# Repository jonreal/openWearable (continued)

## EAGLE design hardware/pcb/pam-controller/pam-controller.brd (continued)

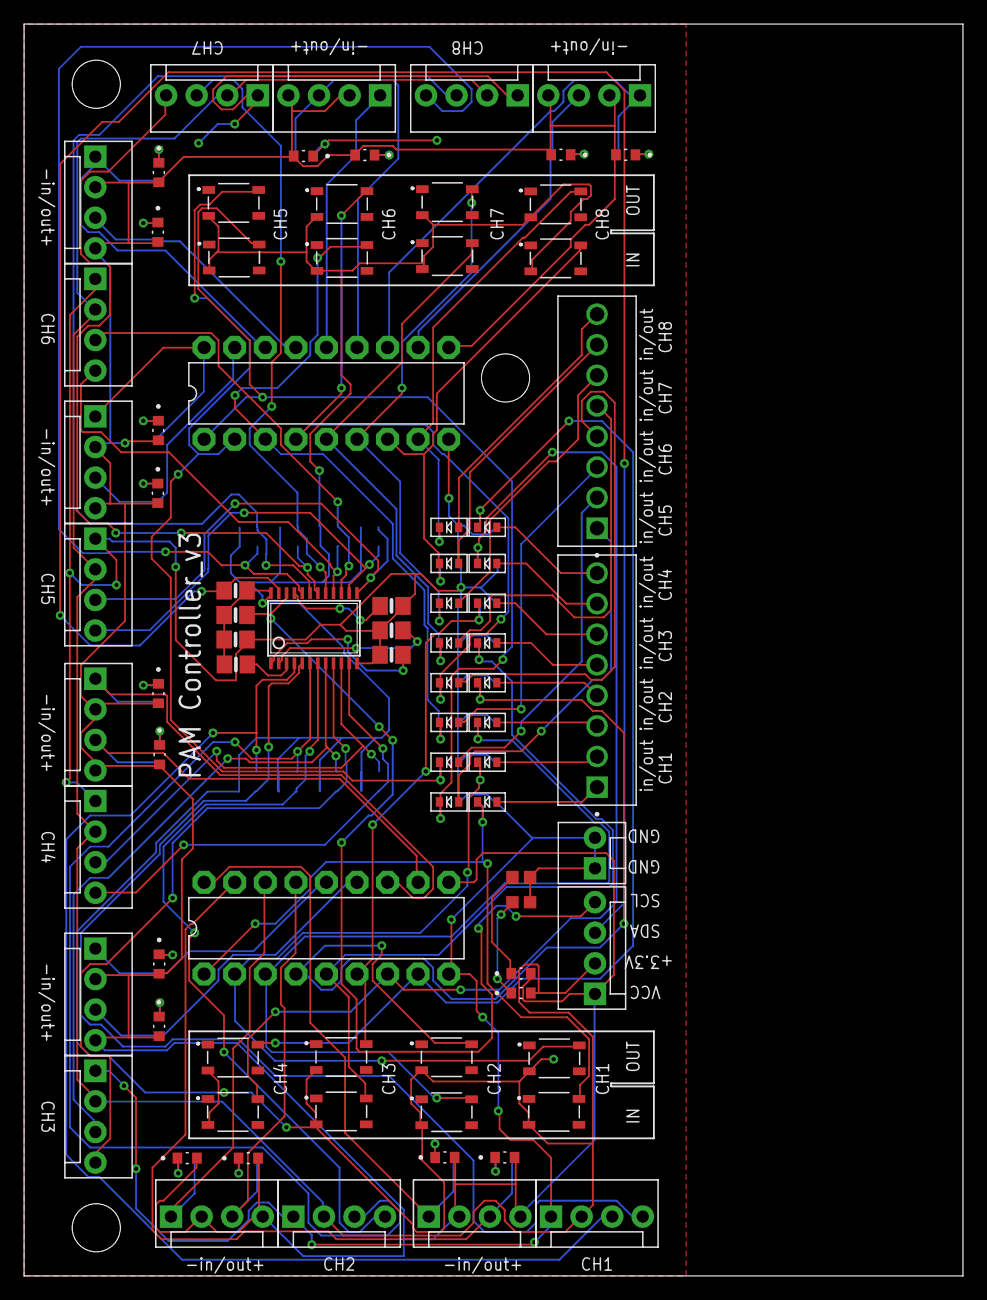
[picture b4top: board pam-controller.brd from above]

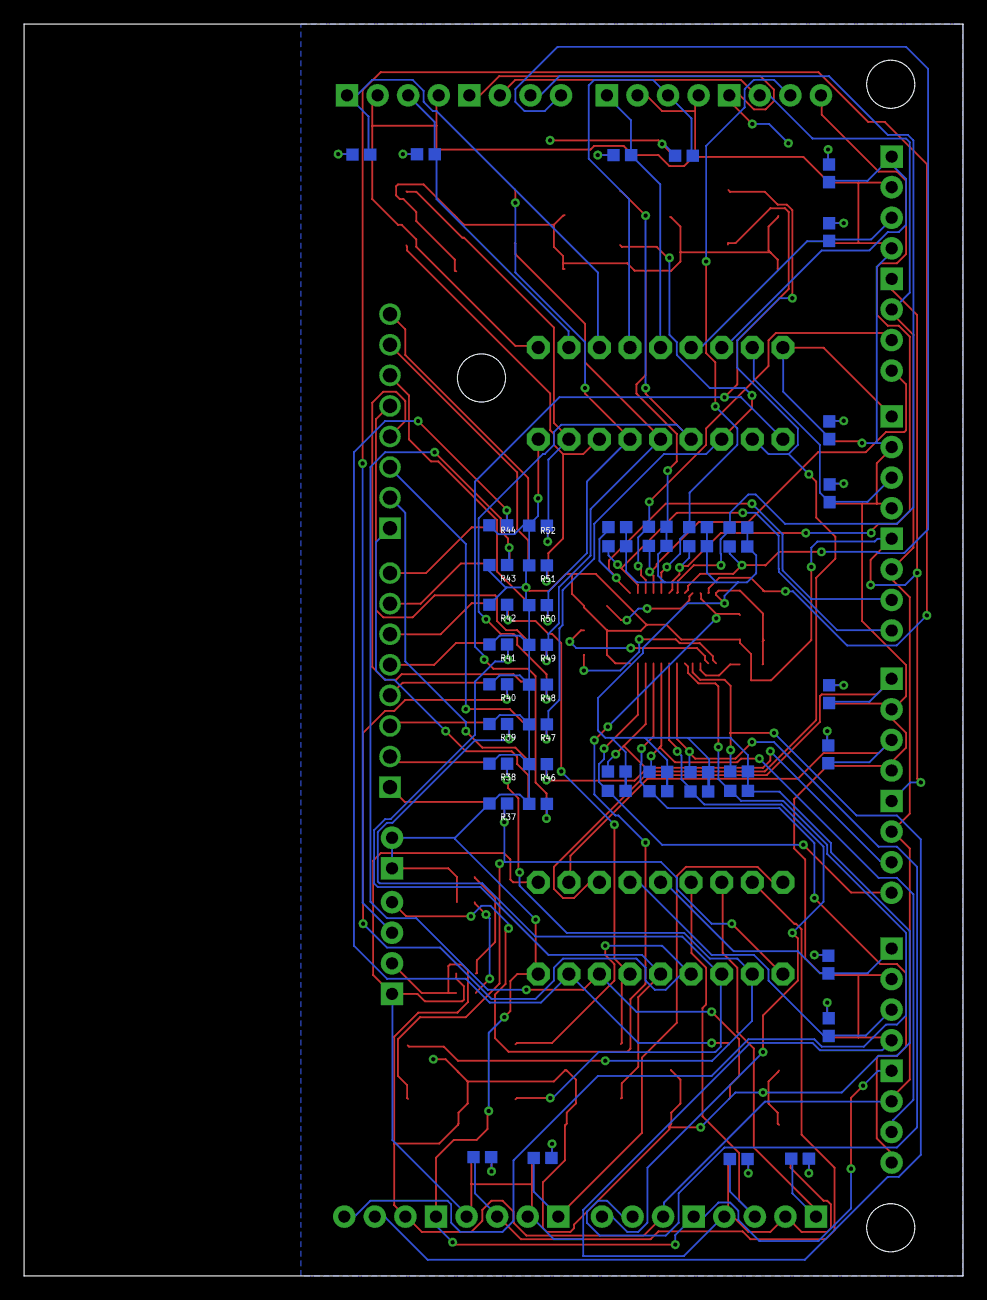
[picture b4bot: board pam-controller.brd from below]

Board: 2 copper layers, 78.0 x 104.0 mm, 130 parts (48 on the bottom side), 91 nets.

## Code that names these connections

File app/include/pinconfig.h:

#ifndef _PINCONFIG_H_
#define _PINCONFIG_H_

#define PWM_PIN     "P8_13"
#define ENB_PIN     "P8_15"
#define DIR_PIN     "P8_17"

#define ADC0        "P9_39"
#define ADC1        "P9_40"
#define ADC2        "P9_37"
#define ADC3        "P9_38"
#define ADC4        "P9_33"
#define ADC5        "P9_36"
#define ADC6        "P9_35"

#define RAD2DEG(X)    ((180.0/M_PI)*X)
#define DEG2RAD(X)    ((M_PI/180.0)*X)

#define ANGLE_OFFSET DEG2RAD(-10)


#endif

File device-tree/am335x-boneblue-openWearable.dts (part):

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	 */
	ehrpwm2_pins: pinmux_ehrpwm2_pins {
		pinctrl-single,pins = <
			AM33XX_PADCONF(AM335X_PIN_GPMC_AD8, PIN_OUTPUT, MUX_MODE4)		/* (U10) gpmc_ad8.ehrpwm2a - PWM_2A */
			AM33XX_PADCONF(AM335X_PIN_GPMC_AD9, PIN_OUTPUT, MUX_MODE4)		/* (T10) gpmc_ad9.ehrpwm2b - PWM_2B */
		>;
	};
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			AM33XX_PADCONF(AM335X_PIN_MCASP0_ACLKX, PIN_INPUT, MUX_MODE3)		/* (A13) mcasp0_aclkx.spi1_sclk */
			AM33XX_PADCONF(AM335X_PIN_MCASP0_FSX, PIN_INPUT, MUX_MODE3)		/* (B13) mcasp0_fsx.spi1_d0 */
			AM33XX_PADCONF(AM335X_PIN_MCASP0_AXR0, PIN_INPUT, MUX_MODE3)		/* (D12) mcasp0_axr0.spi1_d1 */
			/* AM33XX_PADCONF(AM335X_PIN_MCASP0_AHCLKR, PIN_INPUT, MUX_MODE3) */		/* (C12) mcasp0_ahclkr.spi1_cs0 */
			AM33XX_PADCONF(AM335X_PIN_ECAP0_IN_PWM0_OUT, PIN_INPUT, MUX_MODE2)	/* (C18) ecap0_in_pwm0_out.spi1_cs1 */
		>;
	};

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
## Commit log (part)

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2019-08-16 New branch
2019-08-16 Removed irrelevent apps from thumbsup branch
2019-08-16 Readme for thumbsup
2019-08-16 Removed makefile apps not related to thumbsup
2019-08-16 Readme for thumbsup directions
2019-08-16 Update README.md
    thumbs readme
2019-08-16 Update README.md
    updated readme
2019-08-16 Update README.md
    readme
2019-08-16 Add ctl to change base pressure
2019-08-21 update ros publisher to include sync state
2019-09-20 updated maxon driver
2019-09-24 Haptic module completed
2019-09-29 updated reflex to include minimum sensing pressure, added sine to fix16, added freq sweeps for sys ID
2019-09-30 Update README.md
    updated to include other possible ip addresses
2019-09-30 Updates to thumbsup
2019-10-01 Updates to chirp sweeps
2019-10-03 updated pin png
2019-10-04 updated haptics and sweeps and added tare encoder
2019-10-07 new app for haptuv evauations which includes a reflex instantiation, minor upgrades to reflex and device tree
2019-10-18 Emg updates, sig handling, hapit eval, this commit represent code for subject-014
2019-10-23 Emg complete, working on reflexes
2019-10-24 Updated haptic experiment, this commit is snapshot for exp subject 318
2019-10-28 Updating pwm-dac
2019-11-15 Myo reflex and step respone
2019-11-15 Experiment day commit before
2019-11-15 Commit before experiment
2019-11-15 Updated gui
2019-11-15 updated device tree
2019-11-15 gui stuff
2019-11-18 Upgrades on game play before experiment
2019-11-20 Commit before exp w s318
2019-11-25 Commit for exp s435
2019-11-26 Commit s410
2019-12-03 Commit s412
2019-12-04 Added imu to haptic experiment
2019-12-04 Updated reflex parameters
2019-12-04 Added delay in between i2c calls in imu update
2019-12-04 Commit for s410 note that removed imu during exp
2019-12-09 s435
2019-12-16 Updated m-file process data
2019-12-19 s408
2019-12-23 s422
2020-02-09 Some old changes
2020-02-09 updated the haptic tracking app
2020-07-01 new branch for pafp
2020-07-01 updated embedded_process
2020-07-01 minor
2020-07-01 Added updated embedded_process to this branch
2020-07-06 Updated maxon-sweep and tare-encoder for loading parameters to memory
2020-07-06 Updated pyplotter
2021-09-16 Weird bug from a long time ago I guess
2022-02-15 Branch for equiblrium-point-study
2022-02-16 Readme
2022-02-16 Removed hardware stuff that doesn't apply to this project
2022-07-13 fixed bugs in template
2022-08-11 Add pam-starecase for experimental eval of pams
2022-09-02 Pam starecase plus edits to template
2022-09-08 Updated maxon motor and tare to use the PruLoadParams method
2022-09-09 removed ROS from build, but stored old ros makefile
2022-09-09 Tools for PWM/motor calibration
2022-09-12 Updated haptic-tracking with new motor bias current argument
2022-09-21 Updated udp lib, hostname option
2022-09-21 Completed the udp upgrade and added python udplisterner for demo purposes
2022-09-22 Added py udp listner
2022-09-22 Pam cycle for cylic tests
2022-09-22 Edits
2022-09-23 Updated pam-cycle code, works now!
2022-09-23 Added ros/talker for posterity
2022-10-03 pam-cycle edits
2022-10-03 Library edits -- adc current issue, increase size of log
2023-04-18 Xinyao's first commit
2023-04-21 Xinyao's program with new pam.c file for new functions
2023-05-05 Updated plotter and embedded-process-data
2023-05-05 Added plotter-example
2023-10-11 Added LUT capabilities -- fixed few bugs related to LUT memmap
2023-10-11 Updated makeLut.m
2023-10-11 updated makeLut file output
2023-10-11 Added Lerp for LUTs
2023-10-11 Deleted comments
2023-10-12 Fixed small error in LERP
2023-10-12 Changed LUT scaling to 100
2023-10-12 LUT bug
2024-08-27 Updated, with boneblue, to debian 12.6, updated ti-pru headers, adjusted Makefile per new image and headers, and updated resource-table command
2024-10-10 Updated path to pru lib in Makefile
2024-10-11 Updated device tree for boneblue-openWearable
2024-10-13 Added hx711 driver
2024-10-13 added load-cell-test
2024-10-13 Fixed bugs in new hx711 driver
2024-11-01 Working on boneblack devicetree
2024-11-04 Device tree for bone black.
2024-11-04 Added sample for uEnv.txt
2024-11-14 Servo tests for blue
2024-11-16 Blue servo pins from pru-space
2025-03-04 udp plotter
2025-03-06 Claude re-design Makefiles
2025-03-06 Claude Makefile edits
2025-03-06 Claude Makefile
2025-03-06 Claude Makefiles
2025-03-06 Another claude commit for Makefile refract
2025-03-06 claude mf
2025-03-08 claude still
2025-03-08 clauding
2025-03-08 Claude
2025-03-10 Claude Makefile done
2025-03-11 Claude DMA updated
2025-03-11 Claude dma
2025-04-17 Cleaned up Make
2025-04-17 Readme fixed
2025-04-17 Readme updated
2025-04-17 Readme, finalized
2025-04-18 load-cell-test
2025-04-22 Updated target in template/Makefile
2025-04-24 Cleaned up Makefiles
2025-04-25 Updated resource table headers, removing old things
2025-04-25 Updated .cmd to include global symbols for pointers to shared memory and edit correpsonding files to get that to work
2025-04-29 am64x branch
2025-05-01 Trying to porting OW to j721e
2025-05-02 Added dir for hardware/pcb
2025-05-02 Add ADC amplifier schematic and layout files
2025-05-02 Add PAM controller board and schematic files
2025-05-02 Add pam-controller board and schematic files.
2025-05-16 Compiling and running on bone ai64
2025-05-16 Fixed interrupt for event-7 (IEP timer) on am64x
2025-07-11 sfm4100 massflow driver, working but only at low sampling rates
2025-07-12 sfm4100 update, but still one ~200Hz sample
2025-07-25 Added PWM to device tree
2025-07-29 added SPI1 to device tree
2025-07-30 pwm device tree and test
2025-07-31 spi bus for ads131 -- not yet working
2025-07-31 Still working on spi ads
2025-08-12 hnode code with aligned units
2025-09-07 preparing for sit-to-stand, skeleton is there and functioning
2025-09-09 s1 - SRG-sit-to-stand
2025-09-26 NSF-demo
2026-05-14 Added simple 'evoked-repsonse' for testing evoked reflexes
2026-05-14 guis that weren't commited
2026-06-05 commit changes before big claude refactor
2026-06-05 Just before the upgrade
2026-06-10 Staging tidl device tree
2026-06-14 Evoked responses app
2026-06-14 Small error in evoked-response
2026-06-16 Minor edits to comments
2026-06-16 Old makefile at root rm
2026-06-16 Updated readme to test ruleset
2026-06-16 Added evoked-response app
2026-06-16 edit c7x readme
2026-06-19 Tidying up, before r5f refractor
2026-06-19 Tidy before refactor
2026-06-19 Tidy device tree
2026-06-19 added pinout scraped from https://docs.beagleboard.org/boards/beaglebone/ai-64/04-expansion.html\#pinout-diagrams
2026-06-19 Added pinouts images
2026-06-19 staging r5f dtc
2026-06-19 Staged again
